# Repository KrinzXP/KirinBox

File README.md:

# KirinBox
Lever-less fighting game controller meets rhythm game flavour

This is a work in progress (WIP). Details of this will be updated when I have some more time at hand.

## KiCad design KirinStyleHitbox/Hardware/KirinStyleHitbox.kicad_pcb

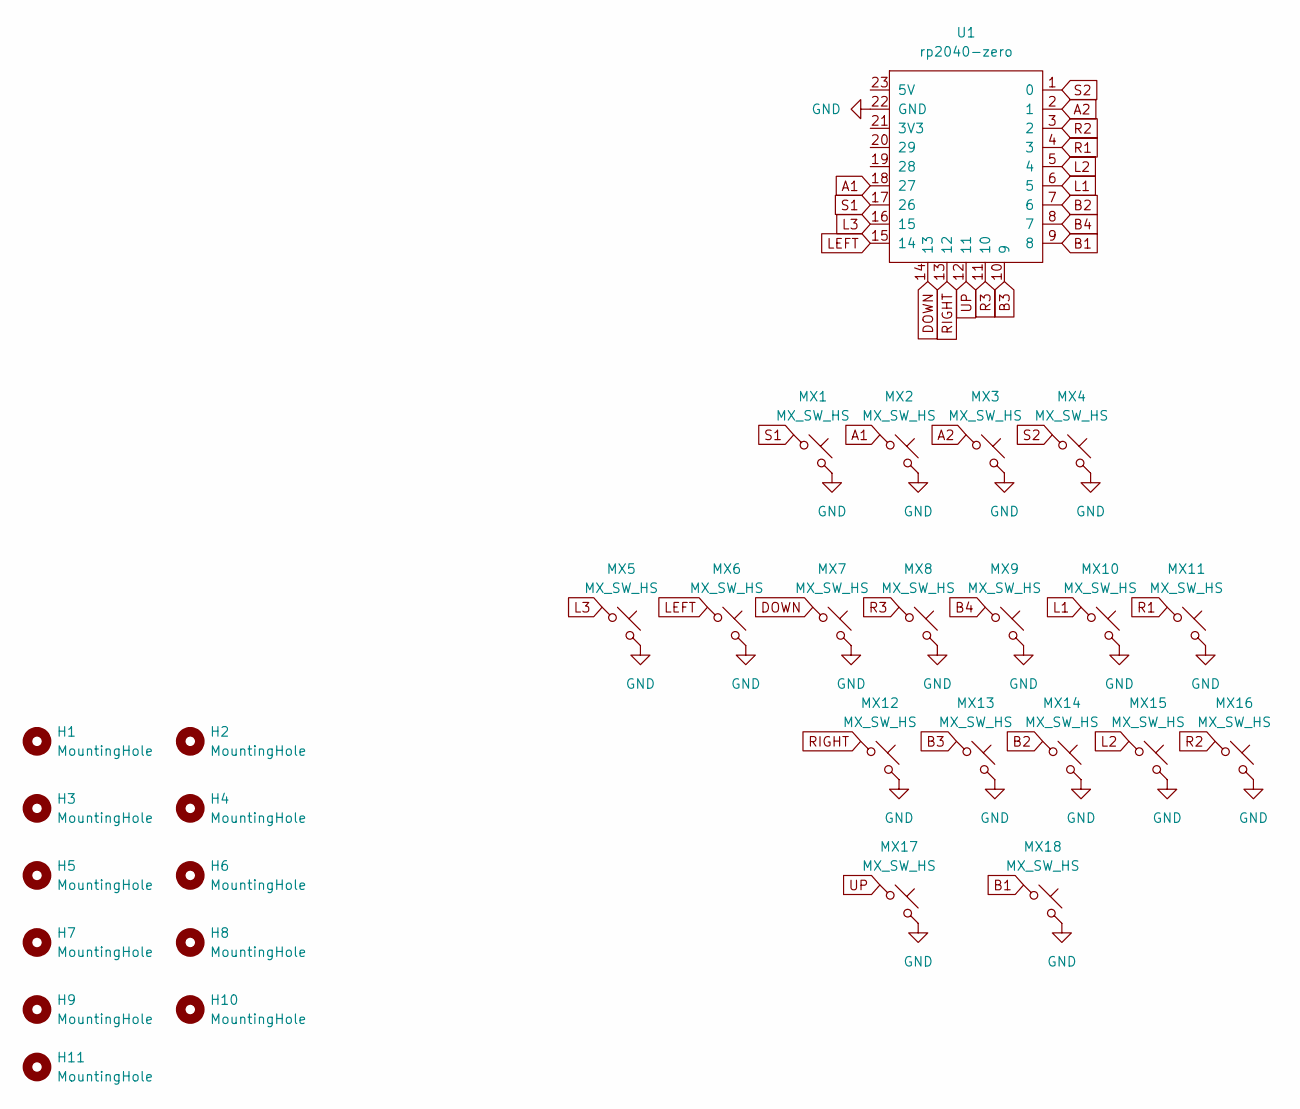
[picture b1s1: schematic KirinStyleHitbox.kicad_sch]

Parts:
H1, H2, H3, H4, H5, H6, H7, H8, H9, H10, H11: MountingHole; MountingHole_3.2mm_M3_Pad_Via
MX1, MX2, MX3, MX4, MX5, MX6, MX7, MX8, MX9, MX10, MX11, MX12, MX13, MX14, MX15, MX16, MX17, MX18: MX_SW_HS; SW_MX_HS_CPG151101S11_1u
U1: rp2040-zero; rp2040-zero-smd

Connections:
A1: MX2.1, U1.18 (27)
A2: MX3.1, U1.2 (1)
B1: MX18.1, U1.9 (8)
B2: MX14.1, U1.7 (6)
B3: MX13.1, U1.10 (9)
B4: MX9.1, U1.8 (7)
DOWN: MX7.1, U1.14 (13)
GND: MX1.2, MX2.2, MX3.2, MX4.2, MX5.2, MX6.2, MX7.2, MX8.2, MX9.2, MX10.2, MX11.2, MX12.2, MX13.2, MX14.2, MX15.2, MX16.2, MX17.2, MX18.2, U1.22 (GND)
L1: MX10.1, U1.6 (5)
L2: MX15.1, U1.5 (4)
L3: MX5.1, U1.16 (15)
LEFT: MX6.1, U1.15 (14)
R1: MX11.1, U1.4 (3)
R2: MX16.1, U1.3 (2)
R3: MX8.1, U1.11 (10)
RIGHT: MX12.1, U1.13 (12)
S1: MX1.1, U1.17 (26)
S2: MX4.1, U1.1 (0)
UP: MX17.1, U1.12 (11)

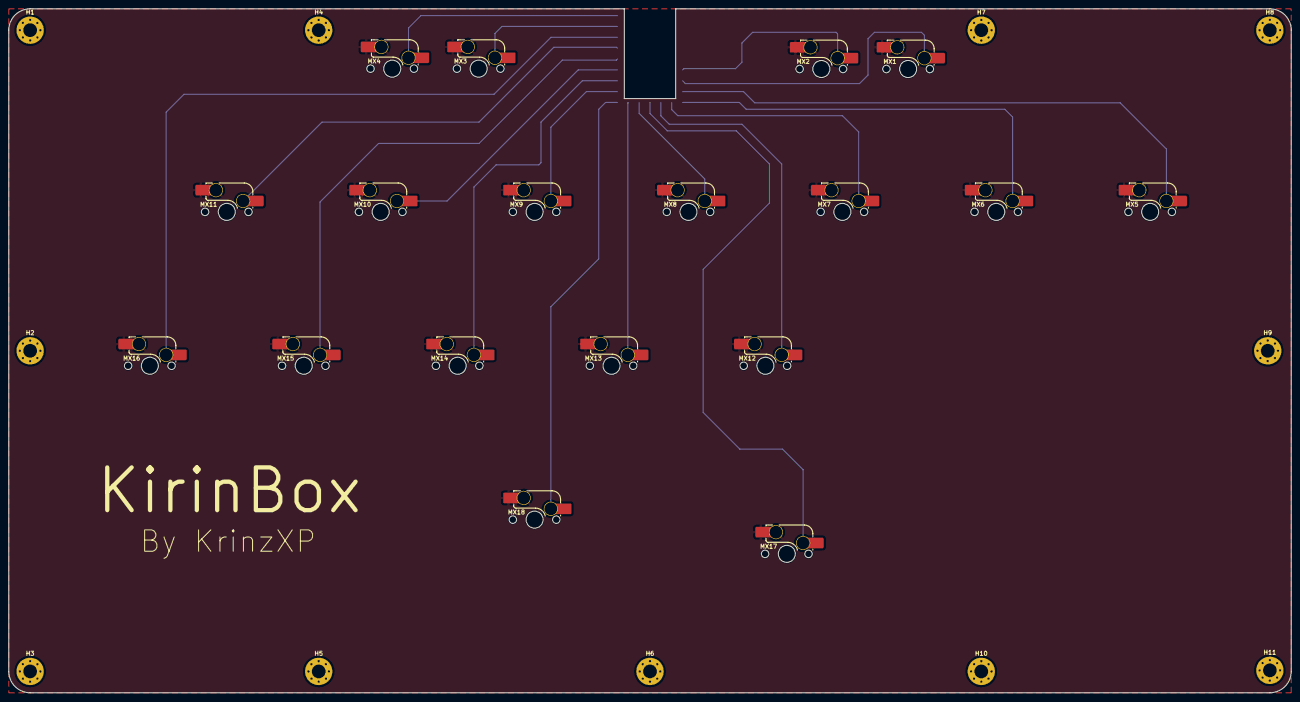
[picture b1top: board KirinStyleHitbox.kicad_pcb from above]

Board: 2 copper layers, 300.0 x 160.0 mm, 30 parts (1 on the bottom side), 19 nets.
